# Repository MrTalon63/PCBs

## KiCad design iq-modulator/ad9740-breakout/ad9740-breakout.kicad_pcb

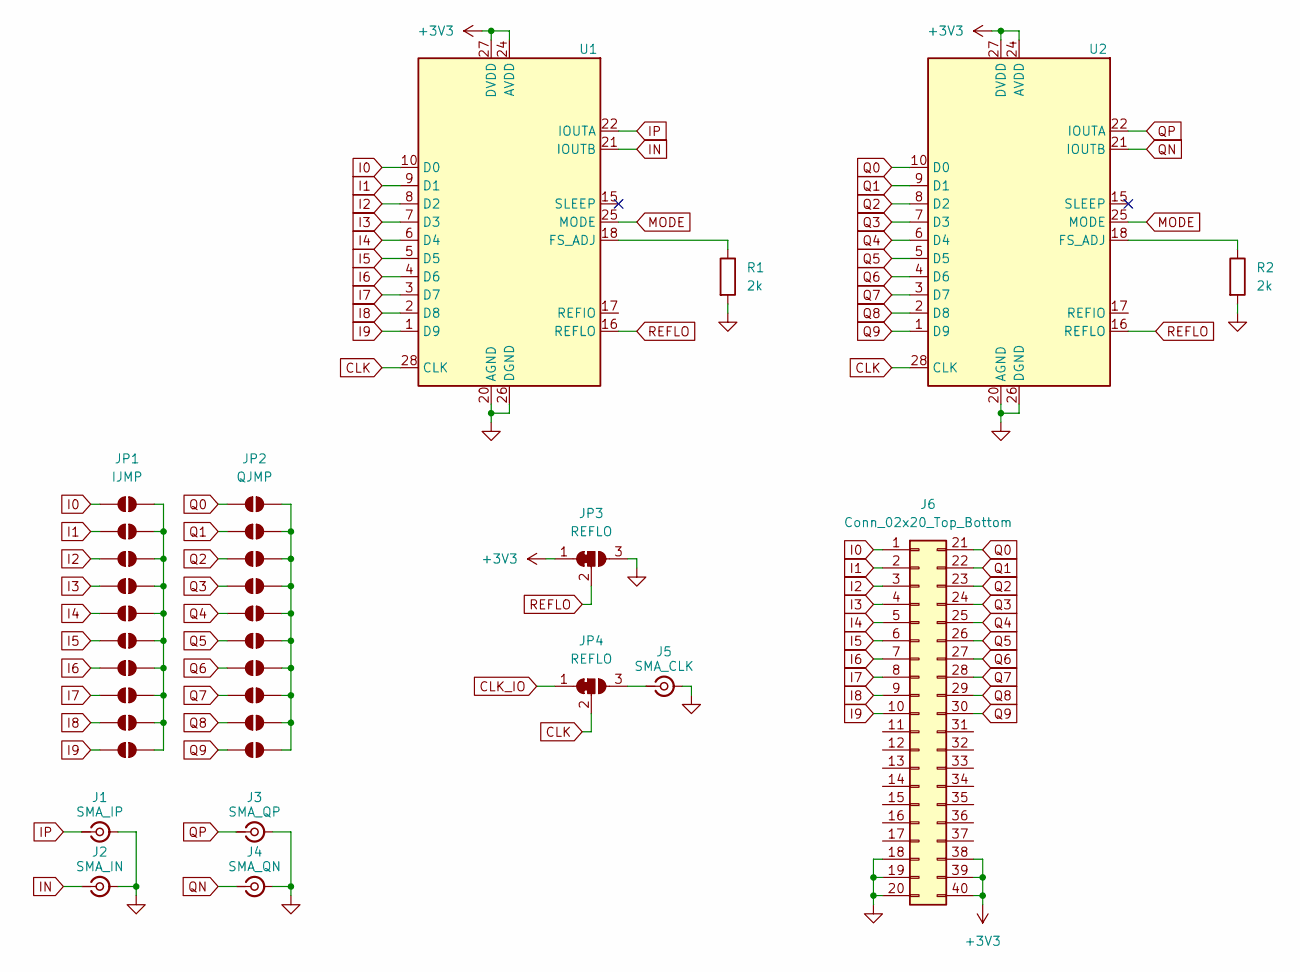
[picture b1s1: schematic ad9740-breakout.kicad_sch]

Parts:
J1: SMA_IP; SMA_Amphenol_132289_EdgeMount
J2: SMA_IN; SMA_Amphenol_132289_EdgeMount
J3: SMA_QP; SMA_Amphenol_132289_EdgeMount
J4: SMA_QN; SMA_Amphenol_132289_EdgeMount
J5: SMA_CLK; SMA_Amphenol_132289_EdgeMount
J6: Conn_02x20_Top_Bottom; PinHeader_2x20_P2.54mm_Vertical
JP1, JP5, JP6, JP7, JP8, JP9, JP10, JP11, JP12, JP13: IJMP; SolderJumper-2_P1.3mm_Open_RoundedPad1.0x1.5mm
JP2, JP14, JP15, JP16, JP17, JP18, JP19, JP20, JP21, JP22: QJMP; SolderJumper-2_P1.3mm_Open_RoundedPad1.0x1.5mm
JP3, JP4: REFLO; SolderJumper-3_P1.3mm_Bridged12_RoundedPad1.0x1.5mm_NumberL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
R1, R2: 2k
U1, U2: TSSOP-28_4.4x9.7mm_P0.65mm

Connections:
+3V3: J6.38, J6.39, J6.40, JP3.1 (A), U1.24 (AVDD), U1.27 (DVDD), U2.24 (AVDD), U2.27 (DVDD)
CLK: JP4.2 (C), U1.28 (CLK), U2.28 (CLK)
CLK_IO: JP4.1 (A)
GND: J1.2 (Ext), J2.2 (Ext), J3.2 (Ext), J4.2 (Ext), J5.2 (Ext), J6.18, J6.19, J6.20, JP3.3 (B), R1.2, R2.2, U1.20 (AGND), U1.26 (DGND), U2.20 (AGND), U2.26 (DGND)
I0: J6.1, JP1.1 (A), U1.10 (D0)
I1: J6.2, JP5.1 (A), U1.9 (D1)
I2: J6.3, JP6.1 (A), U1.8 (D2)
I3: J6.4, JP7.1 (A), U1.7 (D3)
I4: J6.5, JP8.1 (A), U1.6 (D4)
I5: J6.6, JP9.1 (A), U1.5 (D5)
I6: J6.7, JP10.1 (A), U1.4 (D6)
I7: J6.8, JP11.1 (A), U1.3 (D7)
I8: J6.9, JP12.1 (A), U1.2 (D8)
I9: J6.10, JP13.1 (A), U1.1 (D9)
IN: J2.1 (In), U1.21 (IOUTB)
IP: J1.1 (In), U1.22 (IOUTA)
MODE: U1.25 (MODE), U2.25 (MODE)
unnamed: J5.1 (In), JP4.3 (B)
unnamed: JP1.2 (B), JP5.2 (B), JP6.2 (B), JP7.2 (B), JP8.2 (B), JP9.2 (B), JP10.2 (B), JP11.2 (B), JP12.2 (B), JP13.2 (B)
unnamed: JP2.2 (B), JP14.2 (B), JP15.2 (B), JP16.2 (B), JP17.2 (B), JP18.2 (B), JP19.2 (B), JP20.2 (B), JP21.2 (B), JP22.2 (B)
unnamed: R1.1, U1.18 (FS_ADJ)
unnamed: R2.1, U2.18 (FS_ADJ)
Q0: J6.21, JP2.1 (A), U2.10 (D0)
Q1: J6.22, JP14.1 (A), U2.9 (D1)
Q2: J6.23, JP15.1 (A), U2.8 (D2)
Q3: J6.24, JP16.1 (A), U2.7 (D3)
Q4: J6.25, JP17.1 (A), U2.6 (D4)
Q5: J6.26, JP18.1 (A), U2.5 (D5)
Q6: J6.27, JP19.1 (A), U2.4 (D6)
Q7: J6.28, JP20.1 (A), U2.3 (D7)
Q8: J6.29, JP21.1 (A), U2.2 (D8)
Q9: J6.30, JP22.1 (A), U2.1 (D9)
QN: J4.1 (In), U2.21 (IOUTB)
QP: J3.1 (In), U2.22 (IOUTA)
REFLO: JP3.2 (C), U1.16 (REFLO), U2.16 (REFLO)

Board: 2 copper layers, 29 parts (0 on the bottom side), 32 nets, no tracks yet.

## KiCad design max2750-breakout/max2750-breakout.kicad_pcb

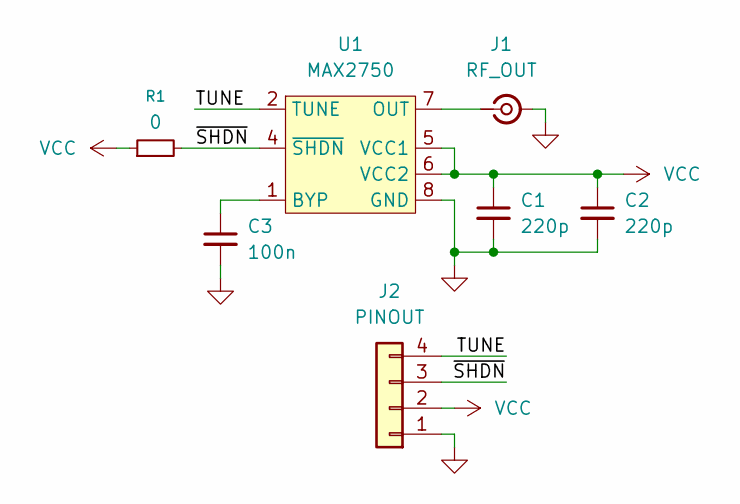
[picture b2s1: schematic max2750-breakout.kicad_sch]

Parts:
C1, C2: 220p; C_0603_1608Metric_Pad1.08x0.95mm_HandSolder
C3: 100n; C_0603_1608Metric_Pad1.08x0.95mm_HandSolder
J1: RF_OUT; SMA_Samtec_SMA-J-P-H-ST-EM1_EdgeMount
J2: PINOUT; PinHeader_1x04_P2.54mm_Vertical
R1: 0; R_0603_1608Metric_Pad0.98x0.95mm_HandSolder
U1: MAX2750; VSSOP-8_3x3mm_P0.65mm

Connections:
/TUNE: J2.4, U1.2 (TUNE)
/~SHDN: J2.3, R1.2, U1.4 (~SHDN)
GND: C1.2, C2.2, C3.2, J1.2 (Ext), J2.1, U1.3 (GND), U1.8 (GND)
unnamed: J1.1 (In), U1.7 (OUT)
unnamed: C3.1, U1.1 (BYP)
VCC: C1.1, C2.1, J2.2, R1.1, U1.5 (VCC1), U1.6 (VCC2)

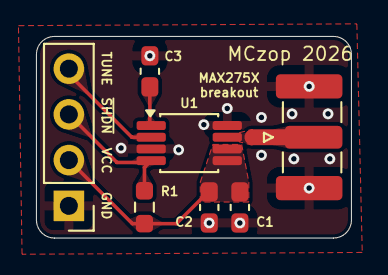
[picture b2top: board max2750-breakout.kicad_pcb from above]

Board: 2 copper layers, 17.5 x 11.2 mm, 7 parts (0 on the bottom side), 6 nets.

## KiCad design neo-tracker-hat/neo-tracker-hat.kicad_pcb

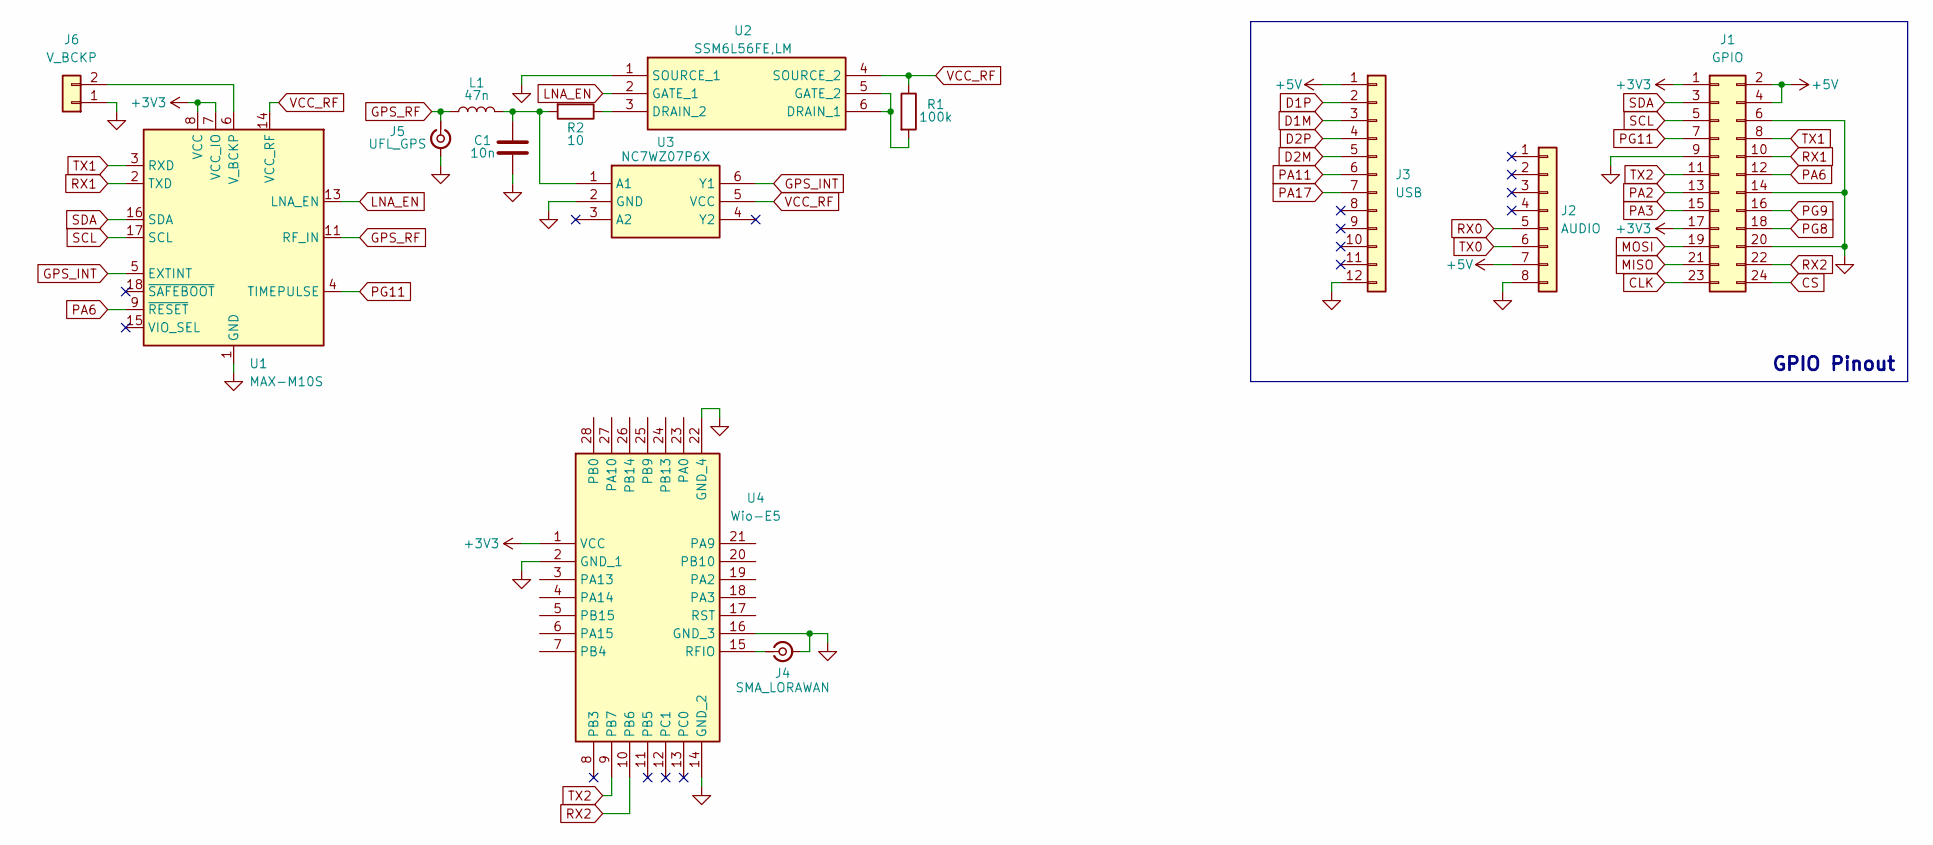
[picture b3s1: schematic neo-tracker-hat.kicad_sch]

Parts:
C1: 10n; C_0603_1608Metric_Pad1.08x0.95mm_HandSolder
J1: GPIO; PinSocket_2x12_P2.54mm_Vertical
J2: AUDIO; PinSocket_1x08_P2.54mm_Vertical
J3: USB; PinSocket_1x12_P2.54mm_Vertical
J4: SMA_LORAWAN; SMA_Amphenol_132289_EdgeMount
J5: UFL_GPS; U.FL_Molex_MCRF_73412-0110_Vertical
J6: V_BCKP; PinSocket_1x02_P2.54mm_Vertical
L1: 47n; L_0603_1608Metric_Pad1.05x0.95mm_HandSolder
R1: 100k; R_0603_1608Metric_Pad0.98x0.95mm_HandSolder
R2: 10; R_0603_1608Metric_Pad0.98x0.95mm_HandSolder
U1: MAX-M10S; ublox_MAX
U2: SSM6L56FE,LM; SOTFL50P160X60-6N; Mouser Part Number 757-SSM6L56FELM
U3: NC7WZ07P6X; SOT65P210X110-6N; Mouser Part Number 512-NC7WZ07P6X
U4: Wio-E5; 317990687; Mouser Part Number 713-317990687

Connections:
+3V3: J1.1, J1.17, U1.7 (VCC_IO), U1.8 (VCC), U4.1 (VCC)
+5V: J1.2, J1.4, J2.7, J3.1
CLK: J1.23
CS: J1.24
D1M: J3.3
D1P: J3.2
D2M: J3.5
D2P: J3.4
GND: C1.2, J1.6, J1.9, J1.14, J1.20, J2.8, J3.12, J4.2 (Ext), J5.2 (Ext), J6.1, U1.1 (GND), U1.10 (GND), U1.12 (GND), U2.1 (SOURCE_1), U3.2 (GND), U4.2 (GND_1), U4.14 (GND_2), U4.16 (GND_3), U4.22 (GND_4)
GPS_INT: U1.5 (EXTINT), U3.6 (Y1)
GPS_RF: J5.1 (In), L1.1, U1.11 (RF_IN)
LNA_EN: U1.13 (LNA_EN), U2.2 (GATE_1)
MISO: J1.21
MOSI: J1.19
unnamed: J4.1 (In), U4.15 (RFIO)
unnamed: J6.2, U1.6 (V_BCKP)
unnamed: R1.2, U2.5 (GATE_2), U2.6 (DRAIN_1)
unnamed: R2.1, U2.3 (DRAIN_2)
unnamed: C1.1, L1.2, R2.2, U3.1 (A1)
PA2: J1.13
PA3: J1.15
PA6: J1.12, U1.9 (~RESET)
PA11: J3.6
PA17: J3.7
PG8: J1.18
PG9: J1.16
PG11: J1.7, U1.4 (TIMEPULSE)
RX0: J2.5
RX1: J1.10, U1.2 (TXD)
RX2: J1.22, U4.10 (PB6)
SCL: J1.5, U1.17 (SCL)
SDA: J1.3, U1.16 (SDA)
TX0: J2.6
TX1: J1.8, U1.3 (RXD)
TX2: J1.11, U4.9 (PB7)
VCC_RF: R1.1, U1.14 (VCC_RF), U2.4 (SOURCE_2), U3.5 (VCC)

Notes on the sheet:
GPIO Pinout

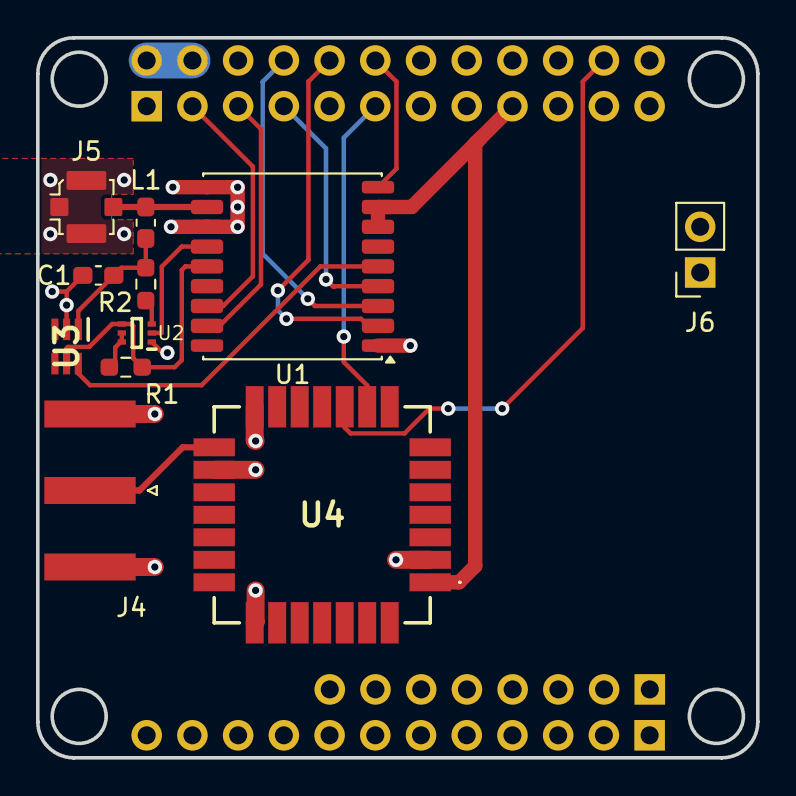
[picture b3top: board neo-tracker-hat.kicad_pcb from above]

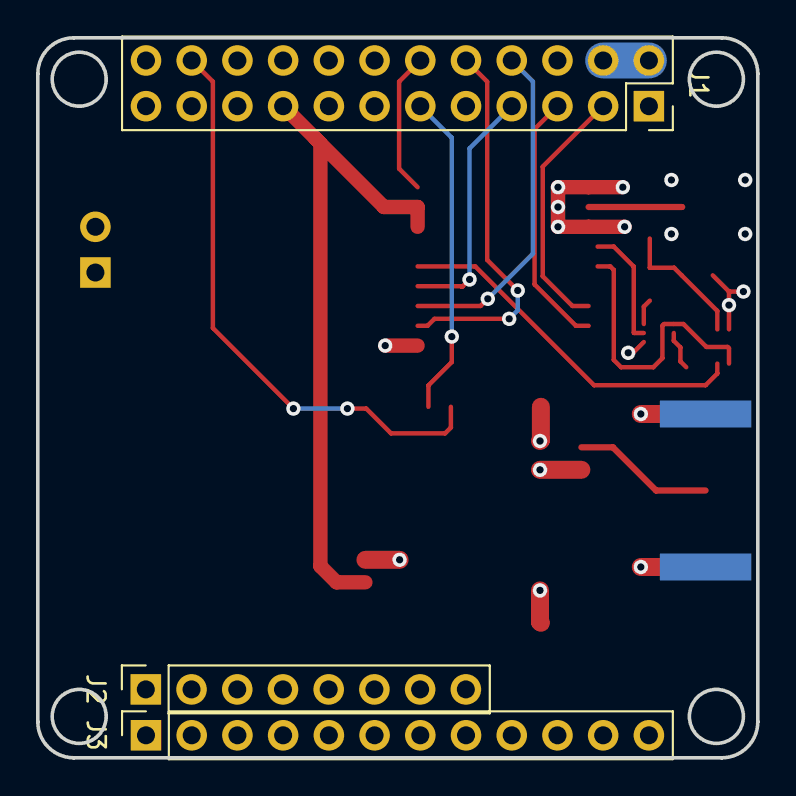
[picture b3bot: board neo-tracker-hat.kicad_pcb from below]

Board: 4 copper layers, 40.0 x 40.0 mm, 18 parts (3 on the bottom side), 20 nets.

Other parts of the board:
H1, H2, H3, H4: MountingHole; MountingHole_3mm

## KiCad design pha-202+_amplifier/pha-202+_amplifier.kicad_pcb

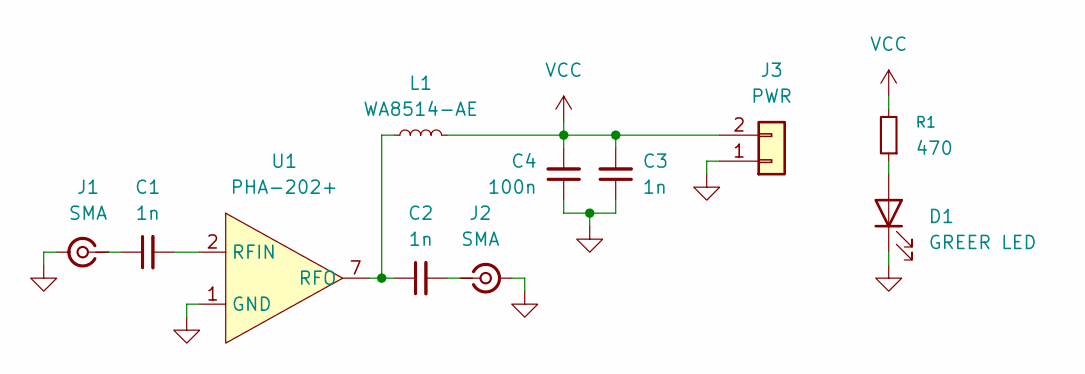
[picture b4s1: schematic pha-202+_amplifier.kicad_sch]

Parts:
C1, C2, C3: 1n; C_0603_1608Metric
C4: 100n; C_0603_1608Metric
D1: GREER LED; LED_0805_2012Metric
J1, J2: SMA; SMA_Samtec_SMA-J-P-H-ST-EM1_EdgeMount
J3: PWR; PinHeader_1x02_P2.54mm_Vertical
L1: WA8514-AE
R1: 470; R_0603_1608Metric
U1: PHA-202+; SON127P600X490X100-9N-D

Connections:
GND: C3.1, C4.1, D1.1 (K), J1.2 (Ext), J2.2 (Ext), J3.1, U1.1 (GND), U1.3 (GND), U1.4 (GND), U1.5 (GND), U1.6 (GND), U1.8 (GND), U1.9 (GND)
unnamed: D1.2 (A), R1.1
unnamed: C1.1, J1.1 (In)
unnamed: C2.2, J2.1 (In)
unnamed: C1.2, U1.2 (RFIN)
unnamed: C2.1, L1.1, U1.7 (RFO)
VCC: C3.2, C4.2, J3.2, L1.2, R1.2

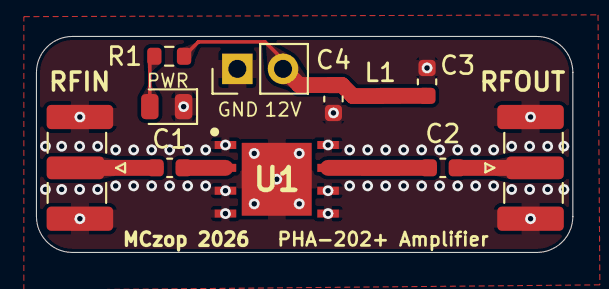
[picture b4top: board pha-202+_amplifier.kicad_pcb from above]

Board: 2 copper layers, 29.8 x 12.0 mm, 11 parts (0 on the bottom side), 7 nets.

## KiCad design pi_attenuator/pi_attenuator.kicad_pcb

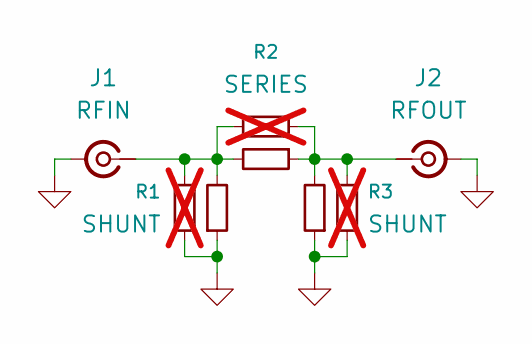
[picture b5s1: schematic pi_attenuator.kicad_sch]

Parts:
J1: RFIN; SMA_Samtec_SMA-J-P-H-ST-EM1_EdgeMount
J2: RFOUT; SMA_Samtec_SMA-J-P-H-ST-EM1_EdgeMount
R1, R3: SHUNT; R_0603_1608Metric
R2: SERIES; R_0603_1608Metric
R4, R5, R6: SERIES; R_0402_1005Metric; not fitted

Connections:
GND: J1.2 (Ext), J2.2 (Ext), R1.1, R3.1, R5.2, R6.2
unnamed: J1.1 (In), R1.2, R2.2, R4.2, R5.1
unnamed: J2.1 (In), R2.1, R3.2, R4.1, R6.1

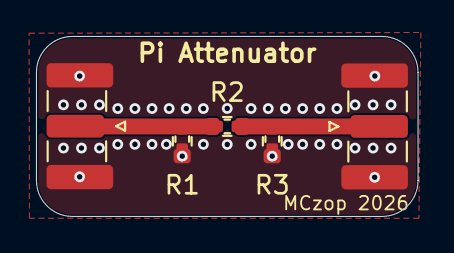
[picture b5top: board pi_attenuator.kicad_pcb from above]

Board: 2 copper layers, 21.2 x 10.0 mm, 8 parts (0 on the bottom side), 3 nets.

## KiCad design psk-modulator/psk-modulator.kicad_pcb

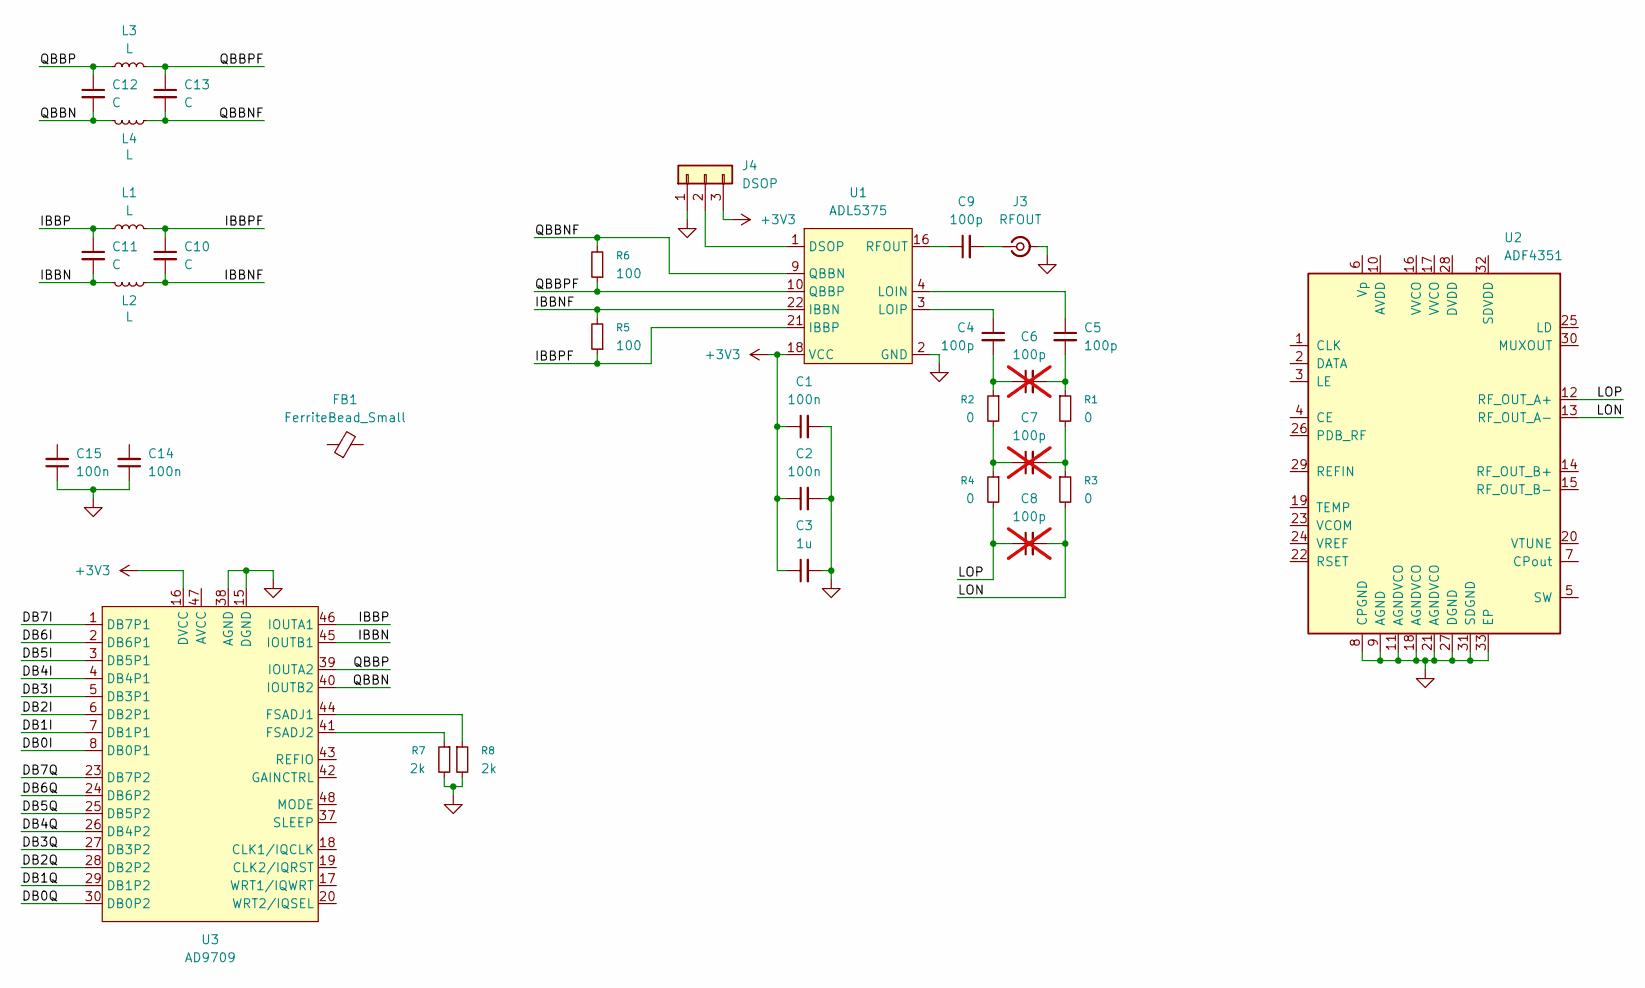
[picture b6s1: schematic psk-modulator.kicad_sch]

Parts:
C1, C2: 100n; C_0603_1608Metric
C3: 1u; C_0603_1608Metric
C4, C5: 100p; C_0603_1608Metric
C6, C7, C8: 100p; C_0402_1005Metric; not fitted
C9: 100p; C_0402_1005Metric
C10, C11, C12, C13: C; C_0402_1005Metric
C14, C15: 100n
FB1: FerriteBead_Small
J3: RFOUT; SMA_Samtec_SMA-J-P-H-ST-EM1_EdgeMount
J4: DSOP; PinHeader_1x03_P2.54mm_Vertical
L1, L2, L3, L4: L; L_0402_1005Metric
R1, R2, R3, R4: 0; L_0402_1005Metric
R5, R6: 100; R_0603_1608Metric
R7, R8: 2k; L_0402_1005Metric
U1: ADL5375; LFCSP-24-1EP_4x4mm_P0.5mm_EP2.5x2.5mm
U2: ADF4351; LFCSP-32-1EP_5x5mm_P0.5mm_EP3.25x3.25mm
U3: AD9709; LQFP-48_7x7mm_P0.5mm

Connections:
+3V3: C1.1, C2.1, C3.1, J4.3, U1.18 (VCC), U1.24 (VCC), U3.16 (DVCC), U3.22 (DVCC)
/DB0I: U3.8 (DB0P1)
/DB0Q: U3.30 (DB0P2)
/DB1I: U3.7 (DB1P1)
/DB1Q: U3.29 (DB1P2)
/DB2I: U3.6 (DB2P1)
/DB2Q: U3.28 (DB2P2)
/DB3I: U3.5 (DB3P1)
/DB3Q: U3.27 (DB3P2)
/DB4I: U3.4 (DB4P1)
/DB4Q: U3.26 (DB4P2)
/DB5I: U3.3 (DB5P1)
/DB5Q: U3.25 (DB5P2)
/DB6I: U3.2 (DB6P1)
/DB6Q: U3.24 (DB6P2)
/DB7I: U3.1 (DB7P1)
/DB7Q: U3.23 (DB7P2)
/IBBN: C11.2, L2.2, U3.45 (IOUTB1)
/IBBNF: C10.2, L2.1, R5.2, U1.22 (IBBN)
/IBBP: C11.1, L1.1, U3.46 (IOUTA1)
/IBBPF: C10.1, L1.2, R5.1, U1.21 (IBBP)
/LON: C8.2, R3.2, U2.13 (RF_OUT_A-)
/LOP: C8.1, R4.2, U2.12 (RF_OUT_A+)
/QBBN: C12.2, L4.2, U3.40 (IOUTB2)
/QBBNF: C13.2, L4.1, R6.2, U1.9 (QBBN)
/QBBP: C12.1, L3.1, U3.39 (IOUTA2)
/QBBPF: C13.1, L3.2, R6.1, U1.10 (QBBP)
GND: C1.2, C2.2, C3.2, C14.1, C15.1, J3.2 (Ext), J4.1, R7.2, R8.2, U1.2 (GND), U1.5 (GND), U1.8 (GND), U1.11 (GND), U1.12 (GND), U1.14 (GND), U1.17 (GND), U1.19 (GND), U1.20 (GND), U1.23 (GND), U1.25 (GND), U2.8 (CPGND), U2.9 (AGND), U2.11 (AGNDVCO), U2.18 (AGNDVCO), U2.21 (AGNDVCO), U2.27 (DGND), U2.31 (SDGND), U2.33 (EP), U3.15 (DGND), U3.21 (DGND), U3.38 (AGND)
unnamed: C4.2, C6.1, R2.1
unnamed: C5.2, C6.2, R1.1
unnamed: C7.1, R2.2, R4.1
unnamed: C7.2, R1.2, R3.1
unnamed: C9.2, J3.1 (In)
unnamed: J4.2, U1.1 (DSOP)
unnamed: C5.1, U1.4 (LOIN)
unnamed: C4.1, U1.3 (LOIP)
unnamed: C9.1, U1.16 (RFOUT)
unnamed: R8.1, U3.44 (FSADJ1)
unnamed: R7.1, U3.41 (FSADJ2)

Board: 2 copper layers, 30 parts (0 on the bottom side), 23 nets, no tracks yet.

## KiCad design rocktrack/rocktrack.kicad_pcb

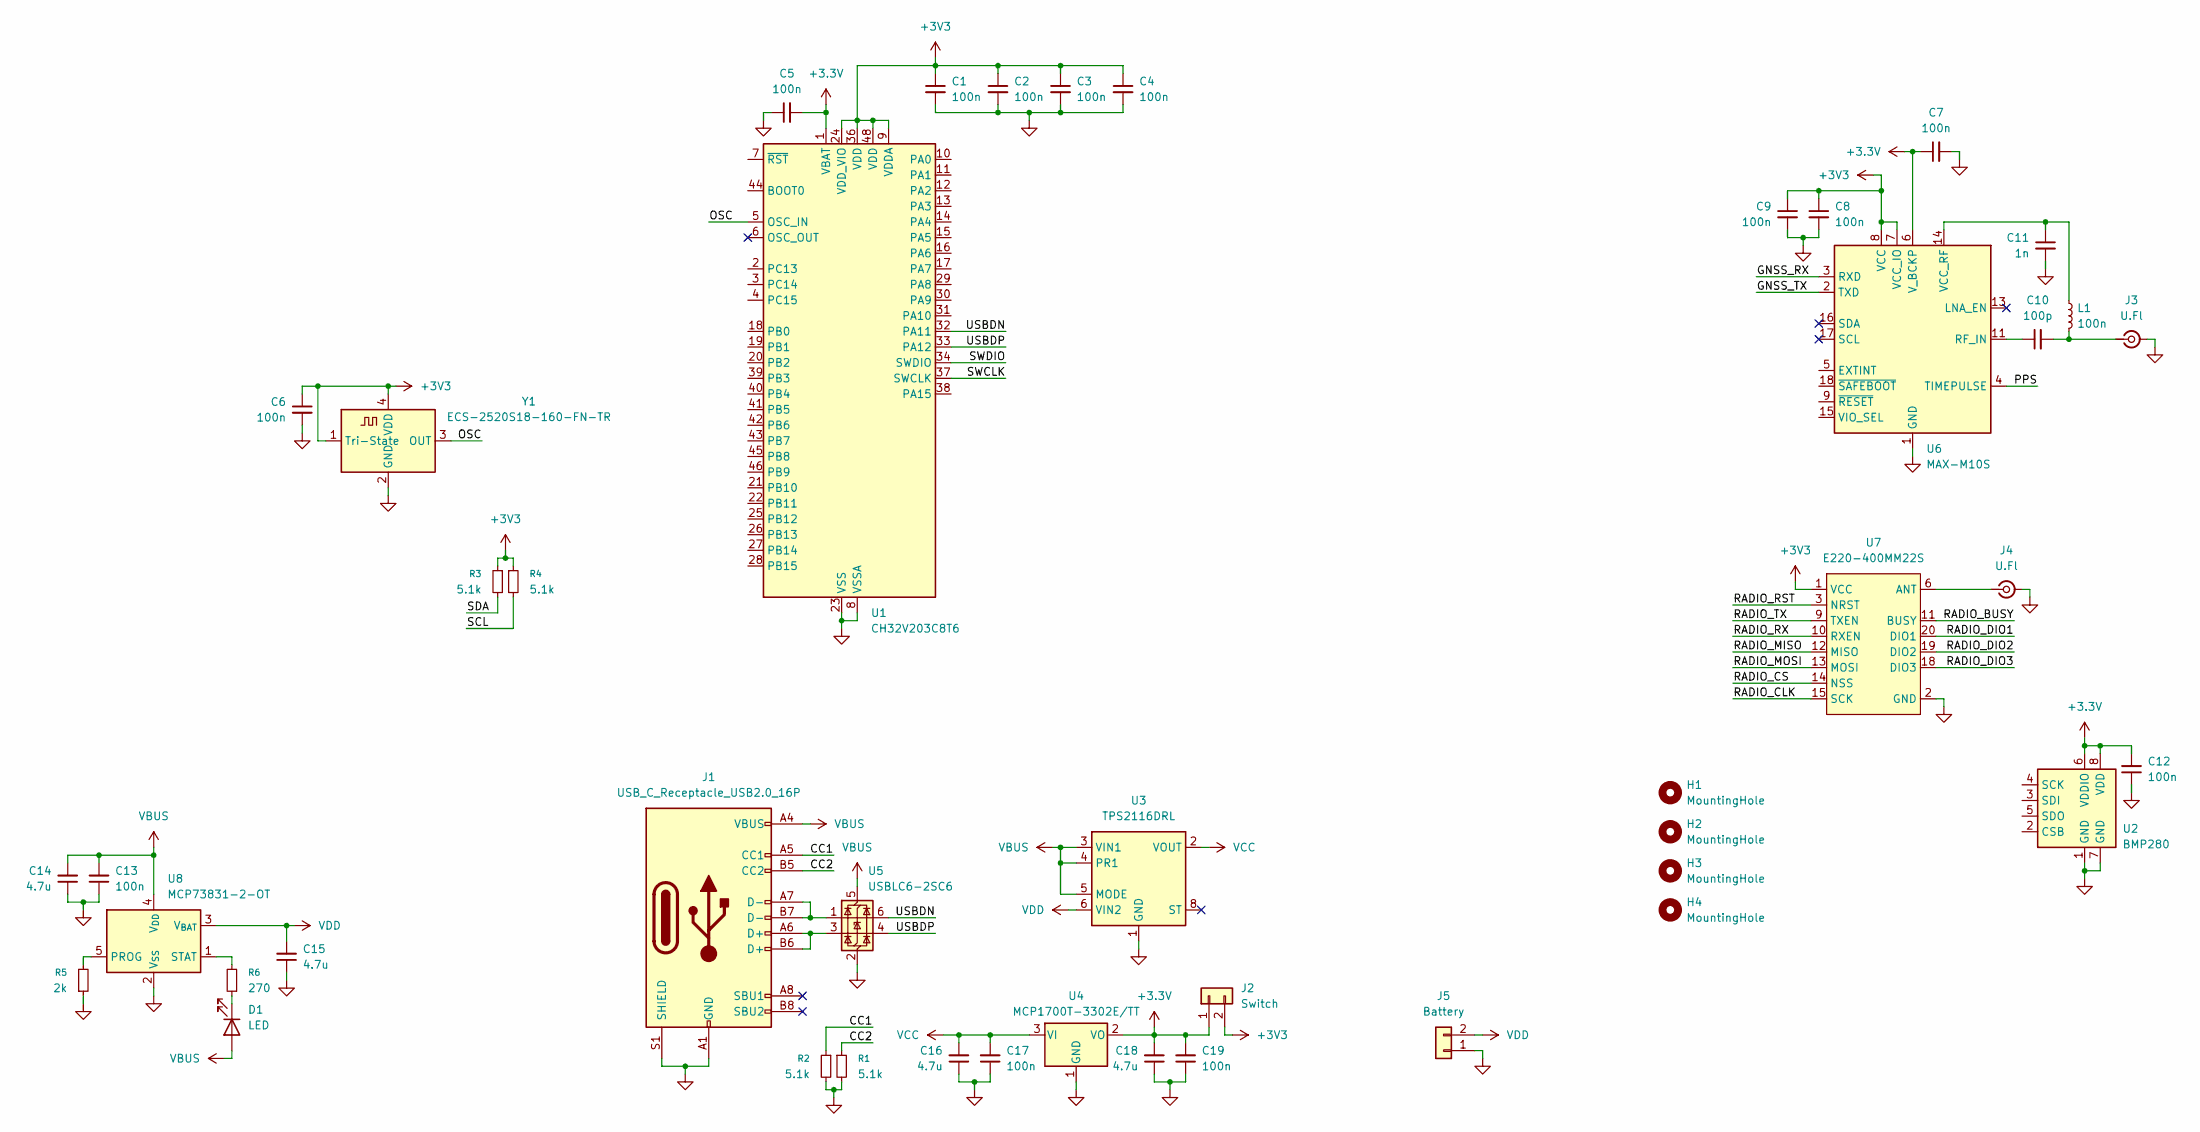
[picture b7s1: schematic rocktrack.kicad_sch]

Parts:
C1, C2, C3, C4, C5, C6, C7, C8, C9, C12, C13, C17, C19: 100n; C_0402_1005Metric
C10: 100p; C_0402_1005Metric
C11: 1n; C_0402_1005Metric
C14, C15, C16, C18: 4.7u; C_0402_1005Metric
D1: LED; LED_0603_1608Metric
H1, H2, H3, H4: MountingHole; MountingHole_2.2mm_M2
J1: USB_C_Receptacle_USB2.0_16P; USB_C_Receptacle_GCT_USB4105-xx-A_16P_TopMnt_Horizontal
J2: Switch; PinSocket_1x02_P2.54mm_Vertical
J3, J4: U.Fl; U.FL_Molex_MCRF_73412-0110_Vertical
J5: Battery; PinSocket_1x02_P2.54mm_Vertical
L1: 100n; L_0402_1005Metric
R1, R2, R3, R4: 5.1k; R_0402_1005Metric
R5: 2k; R_0402_1005Metric
R6: 270; R_0402_1005Metric
U1: CH32V203C8T6; LQFP-48_7x7mm_P0.5mm
U2: BMP280; Bosch_LGA-8_2x2.5mm_P0.65mm_ClockwisePinNumbering
U3: TPS2116DRL; SOT-583-8
U4: MCP1700T-3302E/TT; SOT-23
U5: USBLC6-2SC6; SOT-23-6
U6: MAX-M10S; ublox_MAX
U7: E220-400MM22S; Ebyte MM series
U8: MCP73831-2-OT; SOT-23-5
Y1: ECS-2520S18-160-FN-TR; Oscillator_SMD_ECS_2520MV-xxx-xx-4Pin_2.5x2.0mm

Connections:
+3.3V: C5.2, C7.1, C12.2, C18.2, C19.2, J2.1, U1.1 (VBAT), U2.6 (VDDIO), U2.8 (VDD), U4.2 (VO), U6.6 (V_BCKP)
+3V3: C1.1, C2.1, C3.1, C4.1, C6.1, C8.1, C9.1, J2.2, R3.1, R4.1, U1.9 (VDDA), U1.24 (VDD_VIO), U1.36 (VDD), U1.48 (VDD), U6.7 (VCC_IO), U6.8 (VCC), U7.1 (VCC), Y1.1 (Tri-State), Y1.4 (VDD)
/CC1: J1.A5 (CC1), R2.1
/CC2: J1.B5 (CC2), R1.1
/GNSS_RX: U6.3 (RXD)
/GNSS_TX: U6.2 (TXD)
/OSC: U1.5 (OSC_IN), Y1.3 (OUT)
/PPS: U6.4 (TIMEPULSE)
/RADIO_BUSY: U7.11 (BUSY)
/RADIO_CLK: U7.15 (SCK)
/RADIO_CS: U7.14 (NSS)
/RADIO_DIO1: U7.20 (DIO1)
/RADIO_DIO2: U7.19 (DIO2)
/RADIO_DIO3: U7.18 (DIO3)
/RADIO_MISO: U7.12 (MISO)
/RADIO_MOSI: U7.13 (MOSI)
/RADIO_RST: U7.3 (NRST)
/RADIO_RX: U7.10 (RXEN)
/RADIO_TX: U7.9 (TXEN)
/SCL: R4.2
/SDA: R3.2
/SWCLK: U1.37 (SWCLK)
/SWDIO: U1.34 (SWDIO)
/USBDN: U1.32 (PA11), U5.6 (I/O1)
/USBDP: U1.33 (PA12), U5.4 (I/O2)
GND: C1.2, C2.2, C3.2, C4.2, C5.1, C6.2, C7.2, C8.2, C9.2, C11.2, C12.1, C13.1, C14.1, C15.1, C16.1, C17.1, C18.1, C19.1, J1.A1 (GND), J1.A12 (GND), J1.B1 (GND), J1.B12 (GND), J1.S1 (SHIELD), J3.2 (Ext), J4.2 (Ext), J5.1, R1.2, R2.2, R5.1, U1.8 (VSSA), U1.23 (VSS), U1.35 (VSS), U1.47 (VSS), U2.1 (GND), U2.7 (GND), U3.1 (GND), U4.1 (GND), U5.2 (GND), U6.1 (GND), U6.10 (GND), U6.12 (GND), U7.2 (GND), U7.7 (GND), U7.16 (GND), U8.2 (V_{SS}), Y1.2 (GND)
unnamed: D1.1 (K), R6.1
unnamed: J1.A6 (D+), J1.B6 (D+), U5.3 (I/O2)
unnamed: J1.A7 (D-), J1.B7 (D-), U5.1 (I/O1)
unnamed: C10.2, J3.1 (In), L1.2
unnamed: J4.1 (In), U7.6 (ANT)
unnamed: C10.1, U6.11 (RF_IN)
unnamed: C11.1, L1.1, U6.14 (VCC_RF)
unnamed: R5.2, U8.5 (PROG)
unnamed: R6.2, U8.1 (STAT)
VBUS: C13.2, C14.2, D1.2 (A), J1.A4 (VBUS), J1.A9 (VBUS), J1.B4 (VBUS), J1.B9 (VBUS), U3.3 (VIN1), U3.4 (PR1), U3.5 (MODE), U5.5 (VBUS), U8.4 (V_{DD})
VCC: C16.2, C17.2, U3.2 (VOUT), U3.7 (VOUT), U4.3 (VI)
VDD: C15.2, J5.2, U3.6 (VIN2), U8.3 (V_{BAT})

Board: 2 copper layers, 45 parts (0 on the bottom side), 20 nets, no tracks yet.
